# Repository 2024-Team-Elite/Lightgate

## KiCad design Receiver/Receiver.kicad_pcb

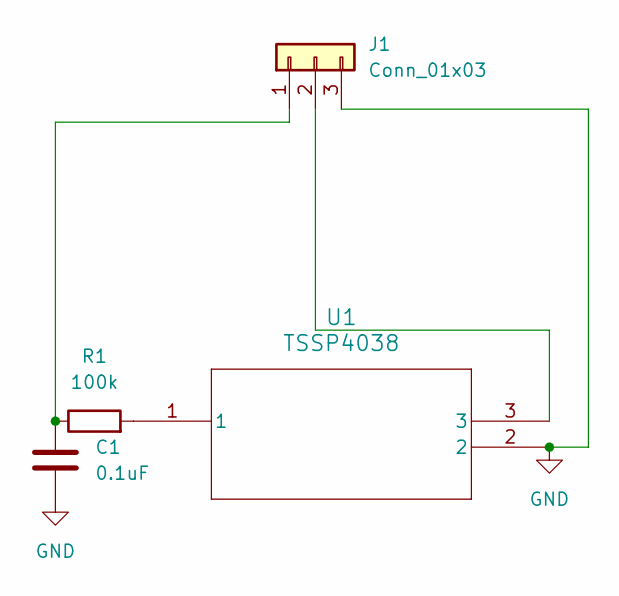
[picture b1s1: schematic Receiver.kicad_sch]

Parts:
C1: 0.1uF; C_0805_2012Metric_Pad1.18x1.45mm_HandSolder
J1: Conn_01x03; JST_XH_B3B-XH-AM_1x03_P2.50mm_Vertical
R1: 100k; R_0805_2012Metric_Pad1.20x1.40mm_HandSolder
U1: TSSP4038; TO_SP4038_VIS

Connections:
GND: C1.2, J1.3, U1.2
unnamed: C1.1, J1.1, R1.1
unnamed: J1.2, U1.3
unnamed: R1.2, U1.1

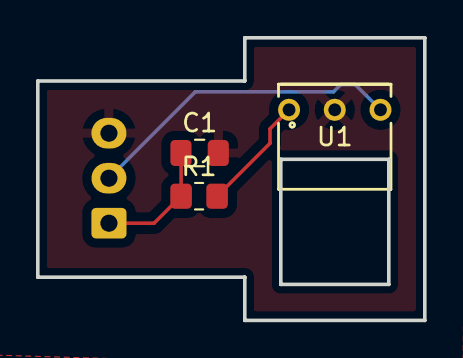
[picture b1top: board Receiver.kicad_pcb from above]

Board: 2 copper layers, 21.5 x 15.7 mm, 4 parts (1 on the bottom side), 4 nets.

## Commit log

2024-03-02 Initial
2024-03-03 Receiver PCB
2024-03-03 gnd fills
2024-04-25 Created Extention for led pcb
2024-04-25 Added low pass filter to reciever pcb
2024-04-26 new changes
